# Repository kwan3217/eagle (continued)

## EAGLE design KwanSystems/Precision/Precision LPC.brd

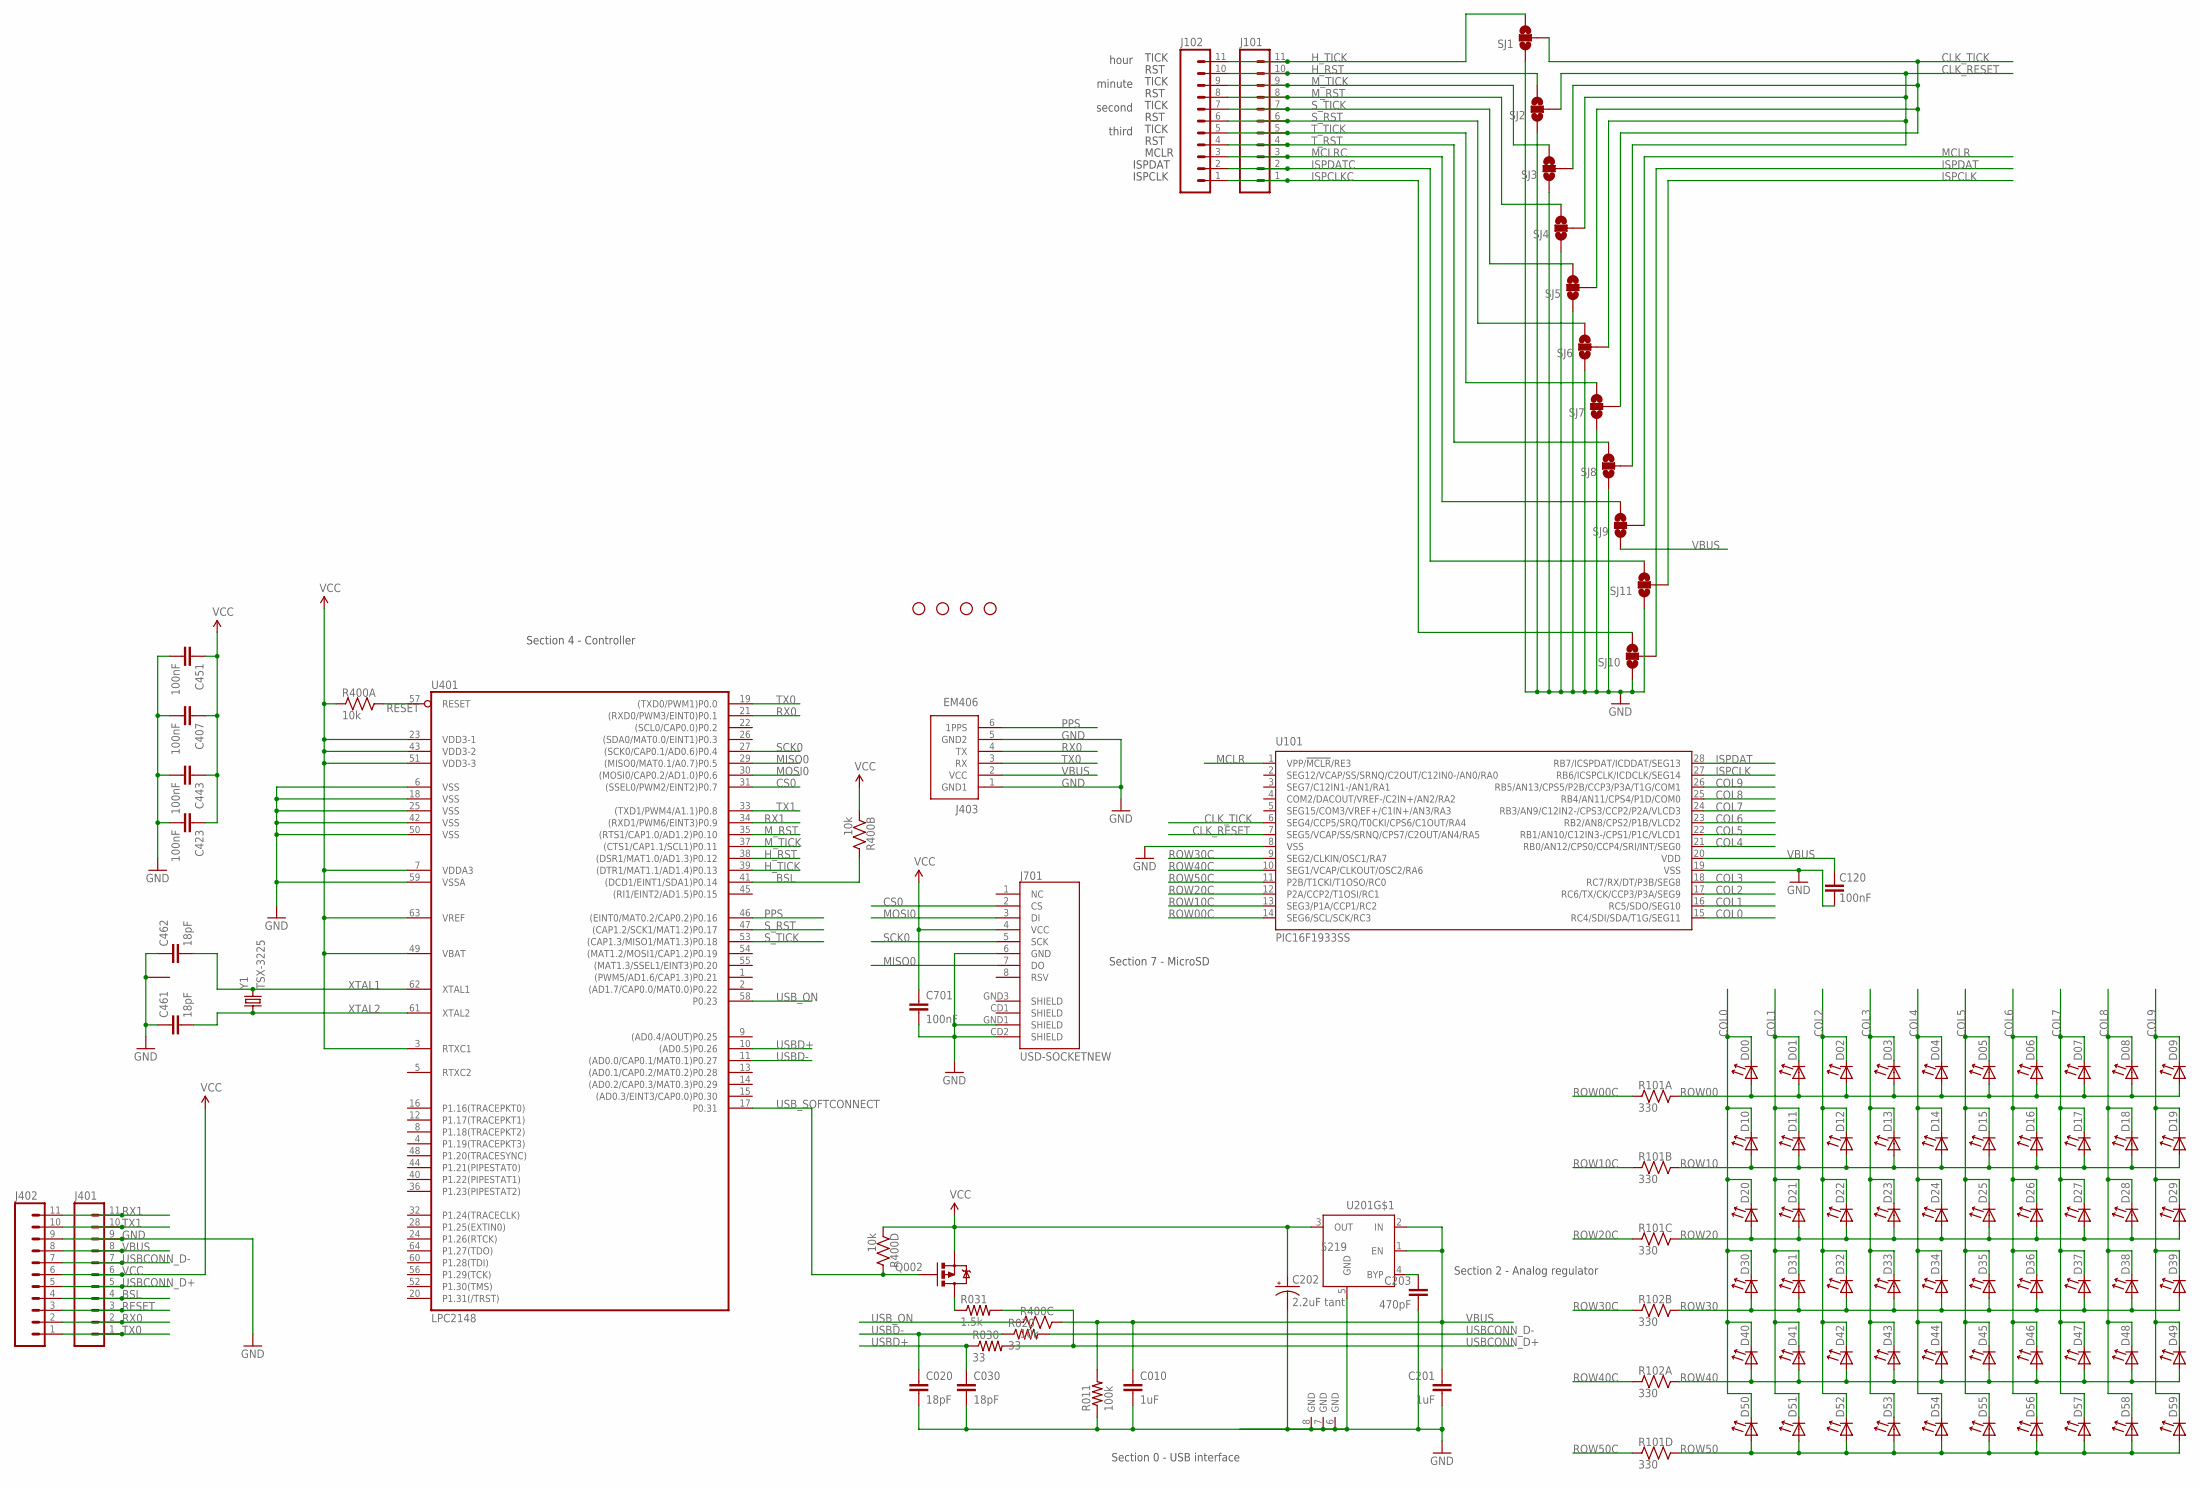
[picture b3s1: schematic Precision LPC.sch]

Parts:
C010, C201: 1uF; 0402-CAP
C020, C030, C461, C462: 18pF; 0402-CAP
C120, C407, C423, C443, C451, C701: 100nF; 0402-CAP
C202: 2.2uF tant; EIA3216
C203: 470pF; 0402-CAP
D00, D01, D02, D03, D04, D05, D06, D07, D08, D09, D10, D11, D12, D13, D14, D15, D16, D17, D18, D19, D20, D21, D22, D23, D24, D25, D26, D27, D28, D29, D30, D31, D32, D33, D34, D35, D36, D37, D38, D39, D40, D41, D42, D43, D44, D45, D46, D47, D48, D49, D50, D51, D52, D53, D54, D55, D56, D57, D58, D59: LED0603_SIDE
J101, J102, J401, J402: M11PTH; 1X11
J403: EM406; EM406@1
J701: USD-SOCKETNEW; MICRO-SD-SOCKET-PP
JP3, JP4, JP5, JP6: STAND-OFF
Q002: PMOS; SOT23-3
R011: 100k; 0402-RES
R020, R030: 33; 0402-RES
R031: 1.5k; 0402-RES
R101, R102: 330; CRA04
R400: 10k; CRA04
SJ1, SJ2, SJ3, SJ4, SJ5, SJ6, SJ7, SJ8, SJ9, SJ10, SJ11: SOLDERJUMPER_2WAYS; SJ_3
U101: PIC16F1933SS; SSOP28
U201: 5219; MSOP08
U401: LPC2148; SQFP-S-10X10-64
Y1: TSX-3225; CRYSTAL_SMD

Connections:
BSL: J401.4, J402.4, R400.7 (2), U401.41 ((DCD1/EINT1/SDA1)P0.14)
CLK_RESET: SJ2.2, SJ4.2, SJ6.2, SJ8.2, U101.7 (SEG5/VCAP/SS/SRNQ/CPS7/C2OUT/AN4/RA5)
CLK_TICK: SJ1.2, SJ3.2, SJ5.2, SJ7.2, U101.6 (SEG4/CCP5/SRQ/T0CKI/CPS6/C1OUT/RA4)
COL0: D00.C, D10.C, D20.C, D30.C, D40.C, D50.C, U101.15 (RC4/SDI/SDA/T1G/SEG11)
COL1: D01.C, D11.C, D21.C, D31.C, D41.C, D51.C, U101.16 (RC5/SDO/SEG10)
COL2: D02.C, D12.C, D22.C, D32.C, D42.C, D52.C, U101.17 (RC6/TX/CK/CCP3/P3A/SEG9)
COL3: D03.C, D13.C, D23.C, D33.C, D43.C, D53.C, U101.18 (RC7/RX/DT/P3B/SEG8)
COL4: D04.C, D14.C, D24.C, D34.C, D44.C, D54.C, U101.21 (RB0/AN12/CPS0/CCP4/SRI/INT/SEG0)
COL5: D05.C, D15.C, D25.C, D35.C, D45.C, D55.C, U101.22 (RB1/AN10/C12IN3-/CPS1/P1C/VLCD1)
COL6: D06.C, D16.C, D26.C, D36.C, D46.C, D56.C, U101.23 (RB2/AN8/CPS2/P1B/VLCD2)
COL7: D07.C, D17.C, D27.C, D37.C, D47.C, D57.C, U101.24 (RB3/AN9/C12IN2-/CPS3/CCP2/P2A/VLCD3)
COL8: D08.C, D18.C, D28.C, D38.C, D48.C, D58.C, U101.25 (RB4/AN11/CPS4/P1D/COM0)
COL9: D09.C, D19.C, D29.C, D39.C, D49.C, D59.C, U101.26 (RB5/AN13/CPS5/P2B/CCP3/P3A/T1G/COM1)
CS0: J701.2 (CS), U401.31 ((SSEL0/PWM2/EINT2)P0.7)
GND: C010.2, C020.2, C030.2, C120.1, C201.2, C202.C (-), C203.2, C407.2, C423.2, C443.2, C451.2, C461.1, C462.1, C701.2, J401.9, J402.9, J403.1 (GND1), J403.5 (GND2), J701.6 (GND), J701.CD2 (SHIELD), J701.GND1 (SHIELD), R011.1, SJ1.1, SJ2.1, SJ3.1, SJ4.1, SJ5.1, SJ6.1, SJ7.1, SJ8.1, SJ10.1, SJ11.1, U101.8 (VSS), U101.19 (VSS), U201.5 (GND), U201.6 (GND), U201.7 (GND), U201.8 (GND), U401.6 (VSS), U401.18 (VSS), U401.25 (VSS), U401.42 (VSS), U401.50 (VSS), U401.59 (VSSA), Y1.2 (1), Y1.4 (1)
H_RST: J101.10, J102.10, SJ2.3, U401.38 ((DSR1/MAT1.0/AD1.3)P0.12)
H_TICK: J101.11, J102.11, SJ1.3, U401.39 ((DTR1/MAT1.1/AD1.4)P0.13)
ISPCLK: SJ11.2, U101.27 (RB6/ICSPCLK/ICDCLK/SEG14)
ISPCLKC: J101.2, J102.2, SJ11.3
ISPDAT: SJ10.2, U101.28 (RB7/ICSPDAT/ICDDAT/SEG13)
ISPDATC: J101.1, J102.1, SJ10.3
MCLR: SJ9.2, U101.1 (VPP/!MCLR!/RE3)
MCLRC: J101.3, J102.3, SJ9.3
MISO0: J701.7 (DO), U401.29 ((MISO0/MAT0.1/A0.7)P0.5)
MOSI0: J701.3 (DI), U401.30 ((MOSI0/CAP0.2/AD1.0)P0.6)
M_RST: J101.8, J102.8, SJ4.3, U401.35 ((RTS1/CAP1.0/AD1.2)P0.10)
M_TICK: J101.9, J102.9, SJ3.3, U401.37 ((CTS1/CAP1.1/SCL1)P0.11)
unnamed: C203.1, U201.4 (BYP)
PPS: J403.6 (1PPS), U401.46 ((EINT0/MAT0.2/CAP0.2)P0.16)
QDRAIN: Q002.3 (D), R031.1
RESET: J401.3, J402.3, R400.8 (2), U401.57 (RESET)
ROW00: D00.A, D01.A, D02.A, D03.A, D04.A, D05.A, D06.A, D07.A, D08.A, D09.A, R101.8 (2)
ROW00C: R101.1, U101.14 (SEG6/SCL/SCK/RC3)
ROW10: D10.A, D11.A, D12.A, D13.A, D14.A, D15.A, D16.A, D17.A, D18.A, D19.A, R101.7 (2)
ROW10C: R101.2 (1), U101.13 (SEG3/P1A/CCP1/RC2)
ROW20: D20.A, D21.A, D22.A, D23.A, D24.A, D25.A, D26.A, D27.A, D28.A, D29.A, R101.6 (2)
ROW20C: R101.3 (1), U101.12 (P2A/CCP2/T1OSI/RC1)
ROW30: D30.A, D31.A, D32.A, D33.A, D34.A, D35.A, D36.A, D37.A, D38.A, D39.A, R102.7 (2)
ROW30C: R102.2 (1), U101.9 (SEG2/CLKIN/OSC1/RA7)
ROW40: D40.A, D41.A, D42.A, D43.A, D44.A, D45.A, D46.A, D47.A, D48.A, D49.A, R102.8 (2)
ROW40C: R102.1, U101.10 (SEG1/VCAP/CLKOUT/OSC2/RA6)
ROW50: D50.A, D51.A, D52.A, D53.A, D54.A, D55.A, D56.A, D57.A, D58.A, D59.A, R101.5 (2)
ROW50C: R101.4 (1), U101.11 (P2B/T1CKI/T1OSO/RC0)
RX0: J401.2, J402.2, J403.4 (TX), U401.21 ((RXD0/PWM3/EINT0)P0.1)
RX1: J401.11, J402.11, U401.34 ((RXD1/PWM6/EINT3)P0.9)
SCK0: J701.5 (SCK), U401.27 ((SCK0/CAP0.1/AD0.6)P0.4)
S_RST: J101.6, J102.6, SJ6.3, U401.47 ((CAP1.2/SCK1/MAT1.2)P0.17)
S_TICK: J101.7, J102.7, SJ5.3, U401.53 ((CAP1.3/MISO1/MAT1.3)P0.18)
TX0: J401.1, J402.1, J403.3 (RX), U401.19 ((TXD0/PWM1)P0.0)
TX1: J401.10, J402.10, U401.33 ((TXD1/PWM4/A1.1)P0.8)
T_RST: J101.4, J102.4, SJ8.3
T_TICK: J101.5, J102.5, SJ7.3
USBCONN_D+: J401.5, J402.5, R030.2, R031.2
USBCONN_D-: J401.7, J402.7, R020.2
USBD+: C030.1, R030.1, U401.10 ((AD0.5)P0.26)
USBD-: C020.1, R020.1, U401.11 ((AD0.0/CAP0.1/MAT0.1)P0.27)
USB_ON: R400.3 (1), U401.58 (P0.23)
USB_SOFTCONNECT: Q002.1 (G), R400.5 (2), U401.17 (P0.31)
VBUS: C010.1, C120.2, C201.1, J401.8, J402.8, J403.2 (VCC), R011.2, R400.6 (2), SJ9.1, U101.20 (VDD), U201.1 (EN), U201.2 (IN)
VCC: C202.A (+), C407.1, C423.1, C443.1, C451.1, C701.1, J401.6, J402.6, J701.4 (VCC), Q002.2 (S), R400.1, R400.2 (1), R400.4 (1), U201.3 (OUT), U401.3 (RTXC1), U401.7 (VDDA3), U401.23 (VDD3-1), U401.43 (VDD3-2), U401.49 (VBAT), U401.51 (VDD3-3), U401.63 (VREF)
XTAL1: C462.2, U401.62 (XTAL1), Y1.3 (2)
XTAL2: C461.2, U401.61 (XTAL2), Y1.1

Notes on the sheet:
TICK
RST
hour
minute
second
third
MCLR
ISPCLK
ISPDAT
Section 0 - USB interface
Section 2 - Analog regulator
Section 4 - Controller
Section 7 - MicroSD

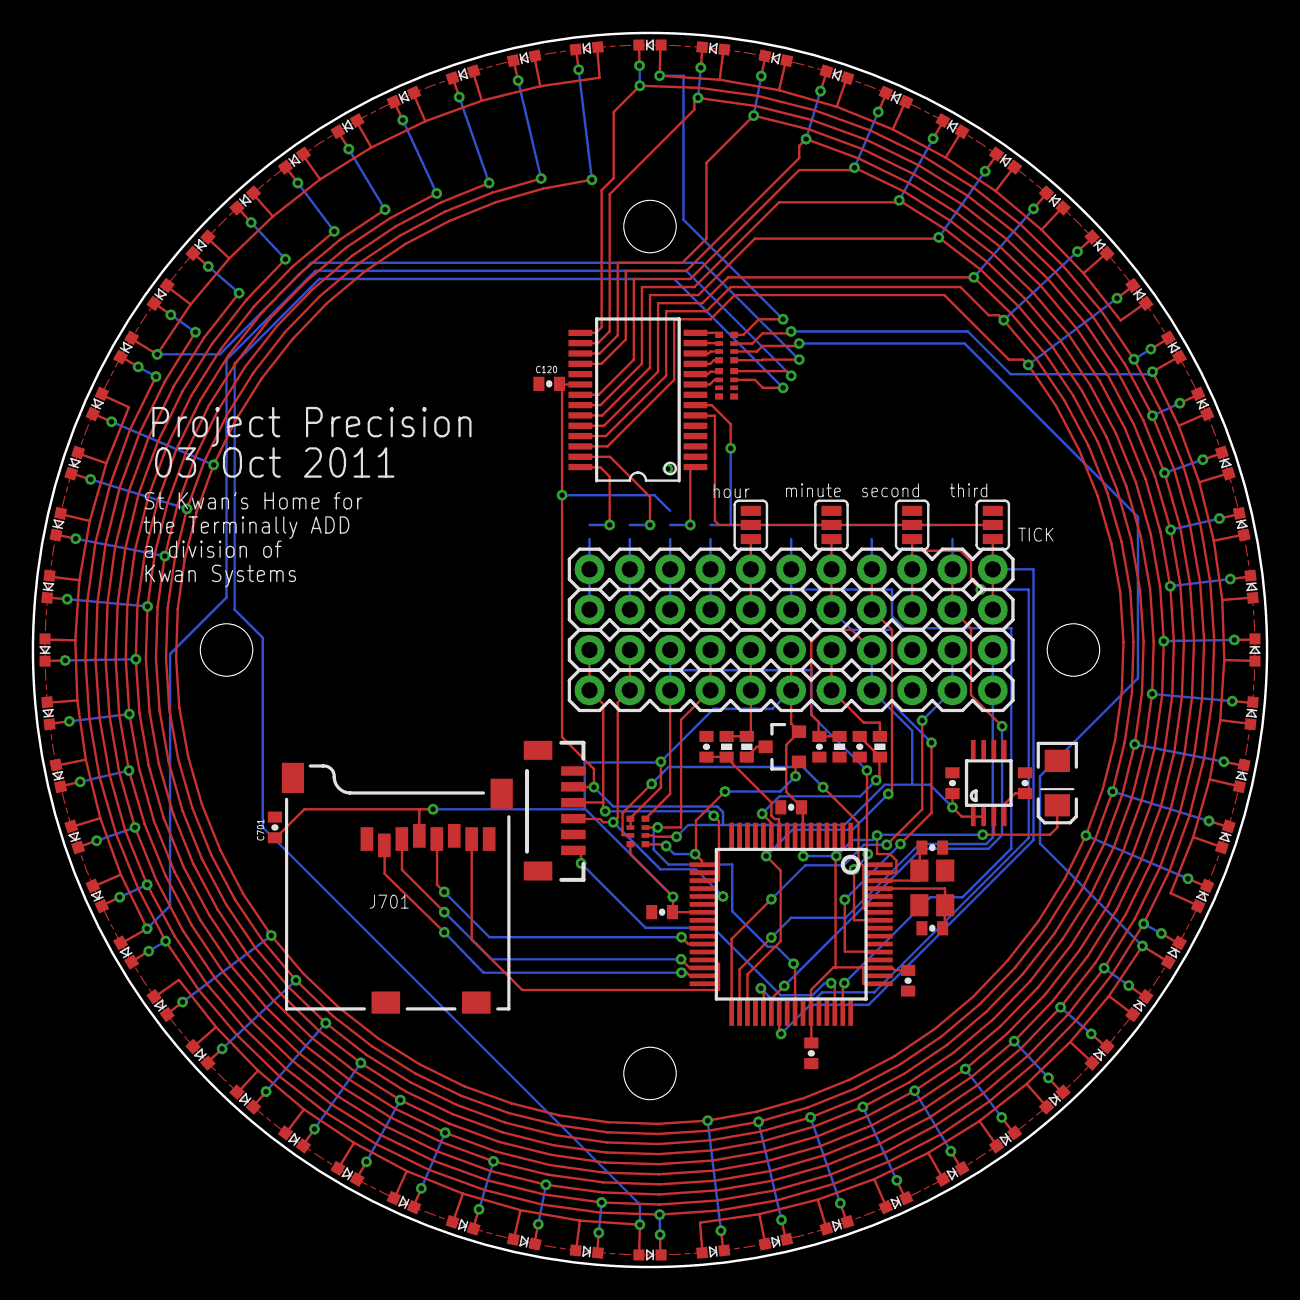
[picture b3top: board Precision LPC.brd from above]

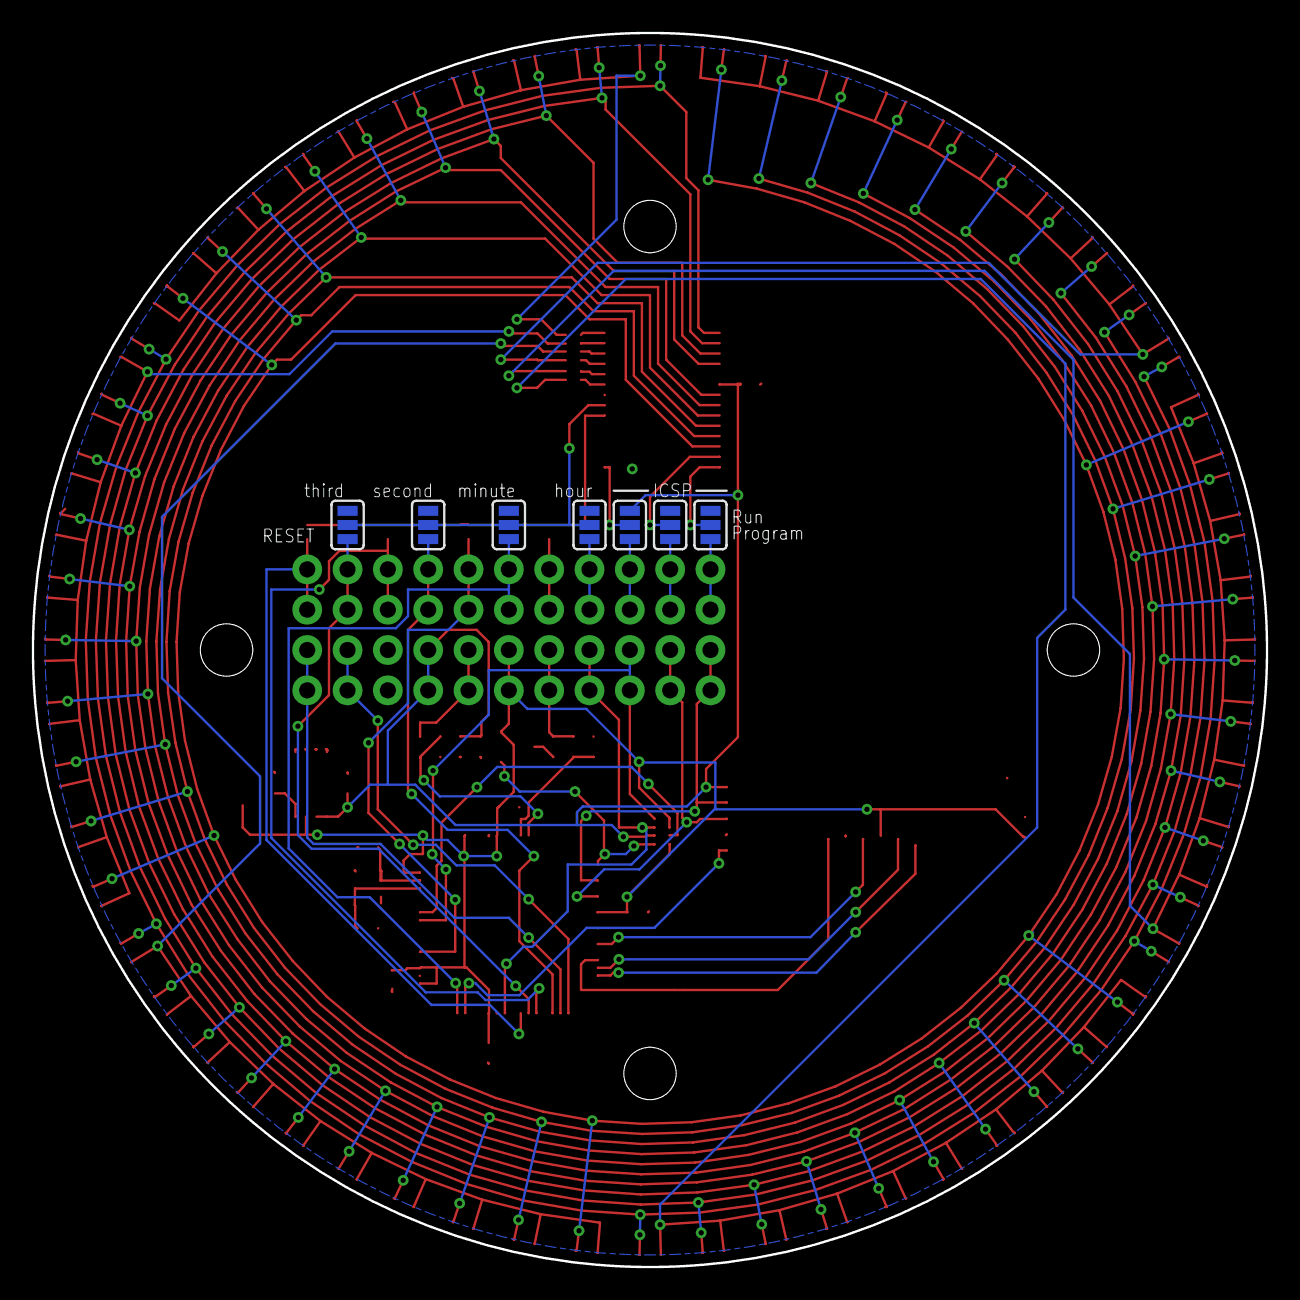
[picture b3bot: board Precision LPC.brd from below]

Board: 2 copper layers, 77.7 x 77.7 mm, 107 parts (7 on the bottom side), 62 nets.
